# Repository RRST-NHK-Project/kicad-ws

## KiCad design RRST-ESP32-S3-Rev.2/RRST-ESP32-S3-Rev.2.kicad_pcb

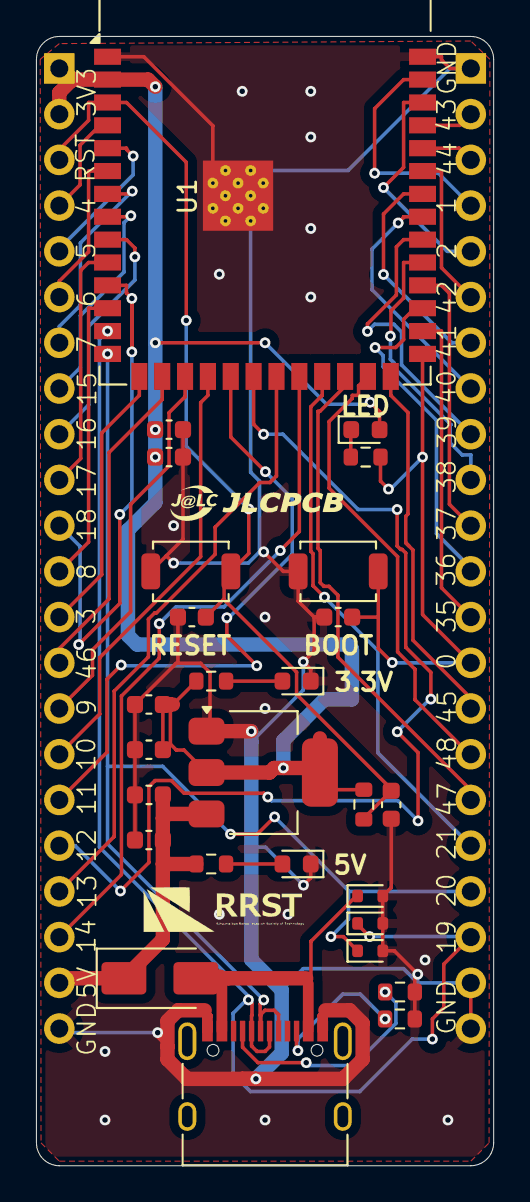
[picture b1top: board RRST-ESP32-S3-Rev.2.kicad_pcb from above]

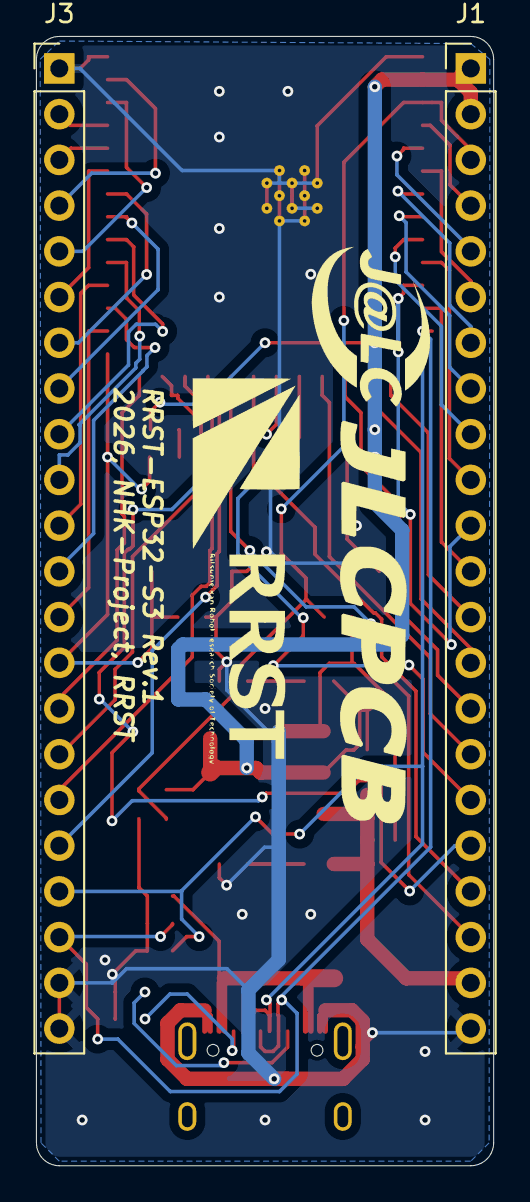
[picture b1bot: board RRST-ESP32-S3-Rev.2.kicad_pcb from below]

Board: 2 copper layers, 25.4 x 62.7 mm, 29 parts (2 on the bottom side), 46 nets.

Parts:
C1, C4, C5: 10uF; C_0603_1608Metric
C2, C3, C6, C7, C8: 100nF; C_0603_1608Metric
C9: 1uF; C_0603_1608Metric
D1, D3, D4: LED; LED_0603_1608Metric
D2: SS14; D_SMA
D5, D6, D8: LESD5D5.0CT1G; D_SOD-523
J1, J3: Conn_01x22_Pin; PinHeader_1x22_P2.54mm_Vertical
J2: USB_C_Receptacle_USB2.0_16P; USB_C_Receptacle_XKB_U262-16XN-4BVC11
R1, R2: 5.1k; R_0603_1608Metric
R3, R4: 5.1K; R_0603_1608Metric
R5: 10k; R_0603_1608Metric
R6: 330; R_0603_1608Metric
SW1, SW2: SW_Push; SW_SPST_TS-1088-xR020
U1: ESP32-S3-WROOM-1
U2: LD1117S33TR_SOT223; SOT-223-3_TabPin2

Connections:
3V3: C3.1, C4.1, C5.1, C6.1, D1.2 (A), J1.1, J1.2, R2.1, R5.1, U1.2 (3V3), U2.2 (VO)
+5V: C1.1, C2.1, D2.1 (K), J1.21, R1.1, U2.3 (VI)
DN: D6.1, J2.A7 (D-), J2.B7 (D-), J3.20, U1.13 (USB_D-)
DP: D8.1, J2.A6 (D+), J2.B6 (D+), J3.19, U1.14 (USB_D+)
EN: C7.1, C9.1, J1.3, R5.2, SW1.2, U1.3 (EN)
GND: C1.2, C2.2, C3.2, C4.2, C5.2, C6.2, C7.2, C8.2, C9.2, D3.1 (K), D4.1 (K), D5.2, D6.2, D8.2, J1.22, J2.A1 (GND), J2.A12 (GND), J2.B1 (GND), J2.B12 (GND), J3.1, J3.21, J3.22, R3.2, R4.2, SW1.1, SW2.1, U1.1 (GND), U1.40 (GND), U1.41 (GND), U2.1 (GND)
IO0: C8.1, J3.14, R6.2, SW2.2, U1.27 (IO0)
IO1: J3.4, U1.39 (IO1)
IO2: J3.5, U1.38 (IO2)
IO3: J1.13, U1.15 (IO3)
IO4: J1.4, U1.4 (IO4)
IO5: J1.5, U1.5 (IO5)
IO6: J1.6, U1.6 (IO6)
IO7: J1.7, U1.7 (IO7)
IO8: J1.12, U1.12 (IO8)
IO9: J1.15, U1.17 (IO9)
IO10: J1.16, U1.18 (IO10)
IO11: J1.17, U1.19 (IO11)
IO12: J1.18, U1.20 (IO12)
IO13: J1.19, U1.21 (IO13)
IO14: J1.20, U1.22 (IO14)
IO15: J1.8, U1.8 (IO15)
IO16: J1.9, U1.9 (IO16)
IO17: J1.10, U1.10 (IO17)
IO18: J1.11, U1.11 (IO18)
IO21: J3.18, U1.23 (IO21)
IO35: J3.13, U1.28 (IO35)
IO36: J3.12, U1.29 (IO36)
IO37: J3.11, U1.30 (IO37)
IO38: J3.10, U1.31 (IO38)
IO39: J3.9, U1.32 (IO39)
IO40: J3.8, U1.33 (IO40)
IO41: J3.7, U1.34 (IO41)
IO42: J3.6, U1.35 (IO42)
IO45: J3.15, U1.26 (IO45)
IO46: J1.14, U1.16 (IO46)
IO47: J3.17, U1.24 (IO47)
IO48: J3.16, U1.25 (IO48)
unnamed: D1.1 (K), R6.1
unnamed: D3.2 (A), R1.2
unnamed: D4.2 (A), R2.2
unnamed: J2.A5 (CC1), R4.1
unnamed: J2.B5 (CC2), R3.1
RXD0: J3.3, U1.36 (RXD0)
TXD0: J3.2, U1.37 (TXD0)
VBUS: D2.2 (A), D5.1, J2.A4 (VBUS), J2.A9 (VBUS), J2.B4 (VBUS), J2.B9 (VBUS)

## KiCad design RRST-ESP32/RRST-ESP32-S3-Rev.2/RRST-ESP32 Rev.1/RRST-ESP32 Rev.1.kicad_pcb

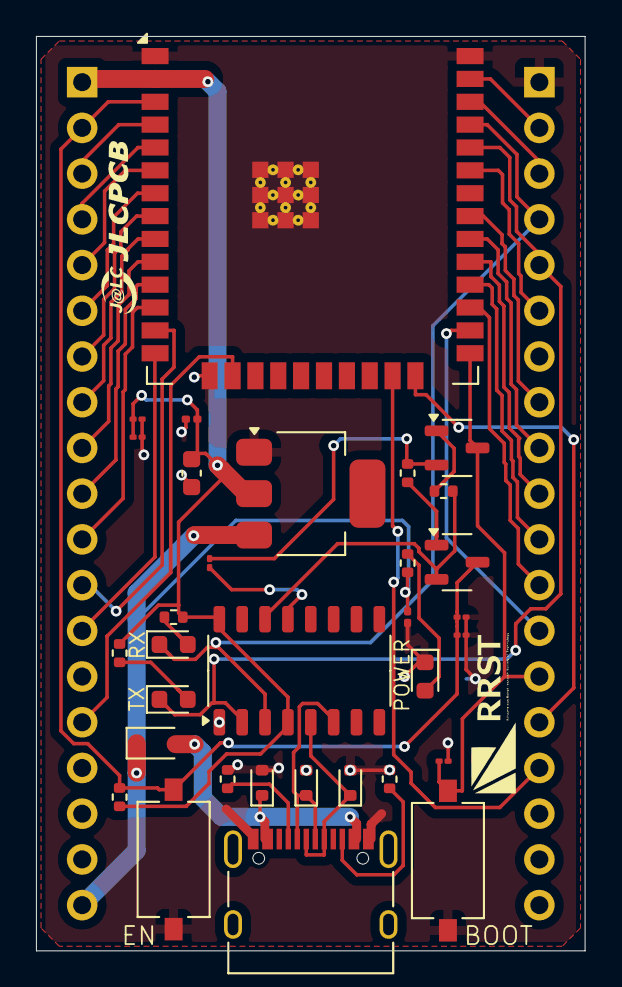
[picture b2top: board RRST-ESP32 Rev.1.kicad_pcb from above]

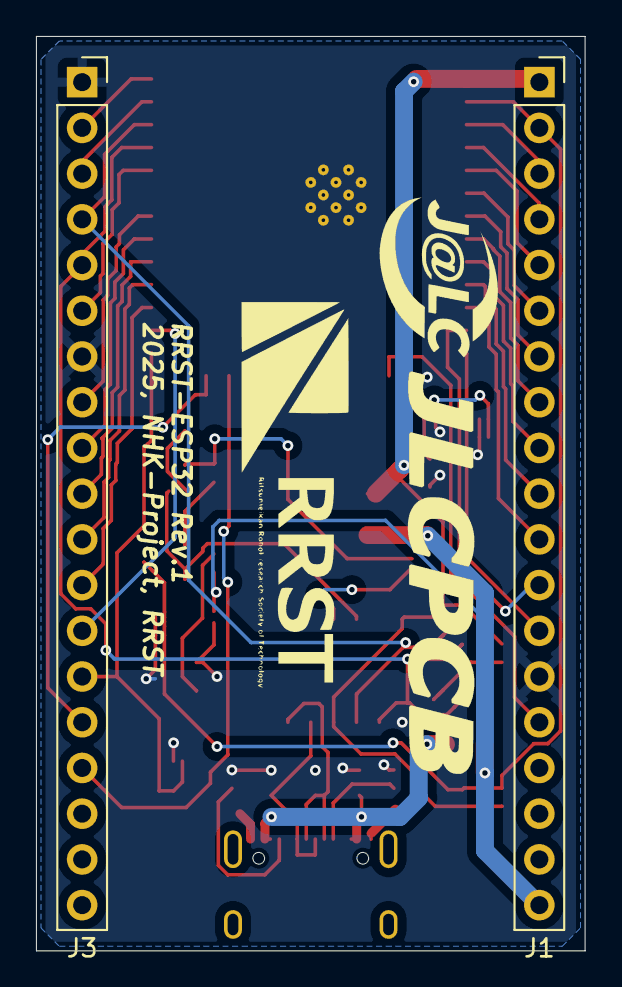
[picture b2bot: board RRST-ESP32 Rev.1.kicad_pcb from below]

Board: 2 copper layers, 30.5 x 50.8 mm, 34 parts (2 on the bottom side), 43 nets.

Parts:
C3: 22uF/10V(20%); C_0603_1608Metric
C4, C6, C7: 0.1uF/50V(10%); C_01005_0402Metric
C5: 0.1uF/50V(10%)(NC); C_01005_0402Metric
C8, C9: 22uF/10V(20%); C_0201_0603Metric
C10, C11: 100nF; C_01005_0402Metric
D1, D2, D4: LESD5D5.0CT1G; D_SOD-523
D3: BAT760-7; D_SOD-323
D5, D6, D7: LED; LED_0603_1608Metric
J1, J3: Conn_01x19_Pin; PinHeader_1x19_P2.54mm_Vertical
J2: USB_C_Receptacle_USB2.0_16P; USB_C_Receptacle_XKB_U262-16XN-4BVC11
Q1, Q2: SS8050-G; SOT-23-3
R1, R2: 1K; R_0402_1005Metric
R3, R4: 5.1K; R_0402_1005Metric
R5, R6, R17: 10K(5%); R_0402_1005Metric
R18: 2K(5%); R_0402_1005Metric
SW1, SW2: SW_Push; SW_Tactile_SPST_NO_Straight_CK_PTS636Sx25SMTRLFS
U1: CH340C; JEITA_SOIC-16_3.9x9.9mm_P1.27mm
U10: ESP32-WROOM-32E
U11: AMS1117-3.3; SOT-223

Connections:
DN: D2.1, J2.A7 (D-), J2.B7 (D-), U1.6 (UD-)
DP: D4.1, J2.A6 (D+), J2.B6 (D+), U1.5 (UD+)
DTR: C11.1, Q2.2, R5.2
EN: C4.1, C7.1, J1.2, Q1.3, R17.2, SW2.2, U10.3 (EN)
EXT_5V: C8.1, D3.C, J1.19, R18.1, U11.3 (VI)
GND: C3.2, C4.2, C5.2, C6.2, C7.2, C8.2, C9.2, C10.2, D1.2, D2.2, D4.2, D5.1 (K), J1.14, J2.A1 (GND), J2.A12 (GND), J2.B1 (GND), J2.B12 (GND), J3.1, J3.7, R3.2, R4.2, SW1.1, SW2.1, U1.1 (GND), U10.1 (GND), U10.15 (GND), U10.38 (GND), U10.39 (GND), U11.1 (GND)
IO0: C5.1, J3.14, Q2.3, SW1.2, U10.25 (IO0)
IO2: J3.15, U10.24 (IO2)
IO4: J3.13, U10.26 (IO4)
IO5: J3.10, U10.29 (IO5)
IO12: J1.13, U10.14 (IO12)
IO13: J1.15, U10.16 (IO13)
IO14: J1.12, U10.13 (IO14)
IO15: J3.16, U10.23 (IO15)
IO16: J3.12, U10.27 (IO16)
IO17: J3.11, U10.28 (IO17)
IO18: J3.9, U10.30 (IO18)
IO19: J3.8, U10.31 (IO19)
IO21: J3.6, U10.33 (IO21)
IO22: J3.3, U10.36 (IO22)
IO23: J3.2, U10.37 (IO23)
IO25: J1.9, U10.10 (IO25)
IO26: J1.10, U10.11 (IO26)
IO27: J1.11, U10.12 (IO27)
IO32: J1.7, U10.8 (IO32)
IO33: J1.8, U10.9 (IO33)
IO34: J1.5, U10.6 (IO34)
IO35: J1.6, U10.7 (IO35)
unnamed: D5.2 (A), R18.2
unnamed: D6.2 (A), R1.2
unnamed: D7.2 (A), R2.2
unnamed: J2.A5 (CC1), R4.1
unnamed: J2.B5 (CC2), R3.1
unnamed: Q1.1, R5.1
unnamed: Q2.1, R6.1
unnamed: C11.2, U1.13 (~DTR)
RTS: Q1.2, R6.2, U1.14 (~RTS)
RX: D6.1 (K), J3.4, U1.3 (RXD), U10.35 (TXD0/IO1)
RXD0/IO3: D7.1 (K), J3.5, U1.2 (TXD), U10.34 (RXD0/IO3)
SENSOR_VN: J1.4, U10.5 (SENSOR_VN)
SENSOR_VP: J1.3, U10.4 (SENSOR_VP)
VBUS: D1.1, D3.A, J2.A4 (VBUS), J2.A9 (VBUS), J2.B4 (VBUS), J2.B9 (VBUS)
VDD33: C3.1, C6.1, C9.1, C10.1, J1.1, R1.1, R2.1, R17.1, U1.4 (V3), U1.16 (VCC), U10.2 (VDD), U11.2 (VO)

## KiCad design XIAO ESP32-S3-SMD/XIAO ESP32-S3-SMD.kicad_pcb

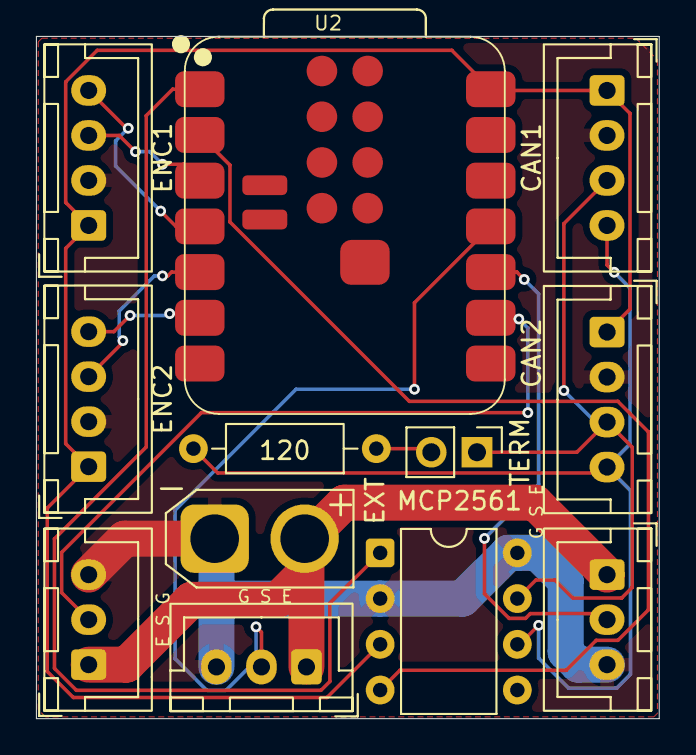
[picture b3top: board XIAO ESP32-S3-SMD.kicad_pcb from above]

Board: 2 copper layers, 34.6 x 37.9 mm, 13 parts (1 on the bottom side), 15 nets.

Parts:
120: 120; R_Axial_DIN0207_L6.3mm_D2.5mm_P10.16mm_Horizontal
CAN1, CAN2: Conn_01x04_Socket; JST_XH_B4B-XH-A_1x04_P2.50mm_Vertical
ENC1: ENC1; JST_XH_B4B-XH-A_1x04_P2.50mm_Vertical
ENC2: ENC2; JST_XH_B4B-XH-A_1x04_P2.50mm_Vertical
ESG1: Conn_01x03_Socket; JST_XH_B3B-XH-A_1x03_P2.50mm_Vertical
EXT: Conn_01x02_Pin; AMASS_XT30U-M_1x02_P5.0mm_Vertical
GSE2, GSE3: Conn_01x03_Socket; JST_XH_B3B-XH-A_1x03_P2.50mm_Vertical
MCP2561: DIP-8_W7.62mm
TERM: R120; PinHeader_1x02_P2.54mm_Vertical
U2: XIAO-ESP32-S3-SMD
soki: LOGO

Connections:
5V0: CAN1.1, CAN2.1, ENC1.1, ENC2.1, MCP2561.3 (Vdd), U2.14 (VBUS)
CANH: CAN1.3, CAN2.3, MCP2561.7 (CANH), TERM.1
CANL: 120.2, CAN1.4, CAN2.4, MCP2561.6 (CANL)
CAN_RX: MCP2561.4 (Rxd), U2.2 (GPIO2_A1_D1)
CAN_TX: MCP2561.1 (Txd), U2.1 (GPIO1_A0_D0)
ENC1_A: ENC1.3, U2.3 (GPIO3_A2_D2)
ENC1_B: ENC1.4, U2.4 (GPIO4_A3_D3)
ENC2_A: ENC2.3, U2.5 (GPIO5_A4_D4_SDA)
ENC2_B: ENC2.4, U2.6 (GPIO6_A5_D5_SCL)
EXT_POWER: ESG1.1, EXT.2, GSE2.1, GSE3.1
GND: CAN1.2, CAN2.2, ENC1.2, ENC2.2, ESG1.3, EXT.1, GSE2.3, GSE3.3, MCP2561.2 (Vss), MCP2561.8 (STBY), U2.13 (GND)
GPIO7: ESG1.2, U2.9 (GPIO7_A8_D8_SCK)
GPIO8: GSE2.2, U2.10 (GPIO8_A9_D9_MISO)
GPIO9: GSE3.2, U2.11 (GPIO9_A10_D10_MOSI)
unnamed: 120.1, TERM.2

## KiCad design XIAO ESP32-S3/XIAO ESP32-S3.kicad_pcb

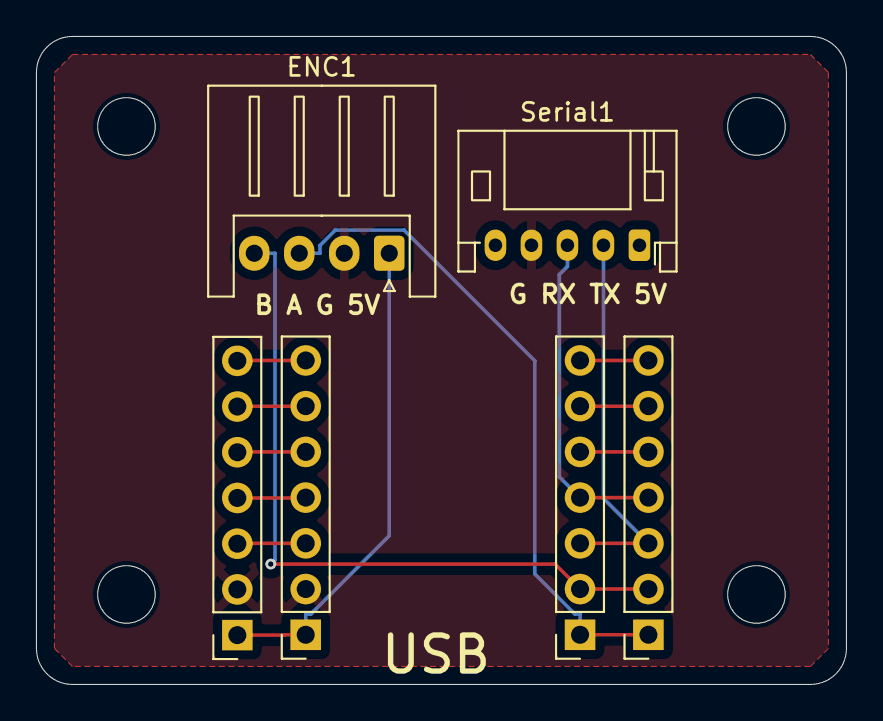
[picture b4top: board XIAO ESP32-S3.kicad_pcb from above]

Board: 2 copper layers, 45.0 x 36.0 mm, 10 parts (0 on the bottom side), 14 nets.

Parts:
ENC1: ENC1; JST_XH_S4B-XH-A_1x04_P2.50mm_Horizontal
J1, J2, J3, J4: Conn_01x07_Socket; PinSocket_1x07_P2.54mm_Vertical
REF1**, REF2**, REF3**, REF4**: MountingHole_3.2mm_M3
Serial1: Serial1; JST_PH_S5B-PH-K_1x05_P2.00mm_Horizontal

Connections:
3V3: J2.3, J4.3
5V: ENC1.1, J2.1, J4.1
ENC1_A: ENC1.3, J1.1, J3.1
ENC1_B: ENC1.4, J1.2, J3.2
GND: ENC1.2, J2.2, J4.2, Serial1.4
GPIO3: J1.3, J3.3, Serial1.2
GPIO4: J1.4, J3.4, Serial1.3
GPIO7: J2.6, J4.6
GPIO8: J2.5, J4.5
NC1: J1.5, J3.5
NC2: J1.6, J3.6
NC3: J1.7, J3.7
NC4: J2.4, J4.4
NC5: J2.7, J4.7

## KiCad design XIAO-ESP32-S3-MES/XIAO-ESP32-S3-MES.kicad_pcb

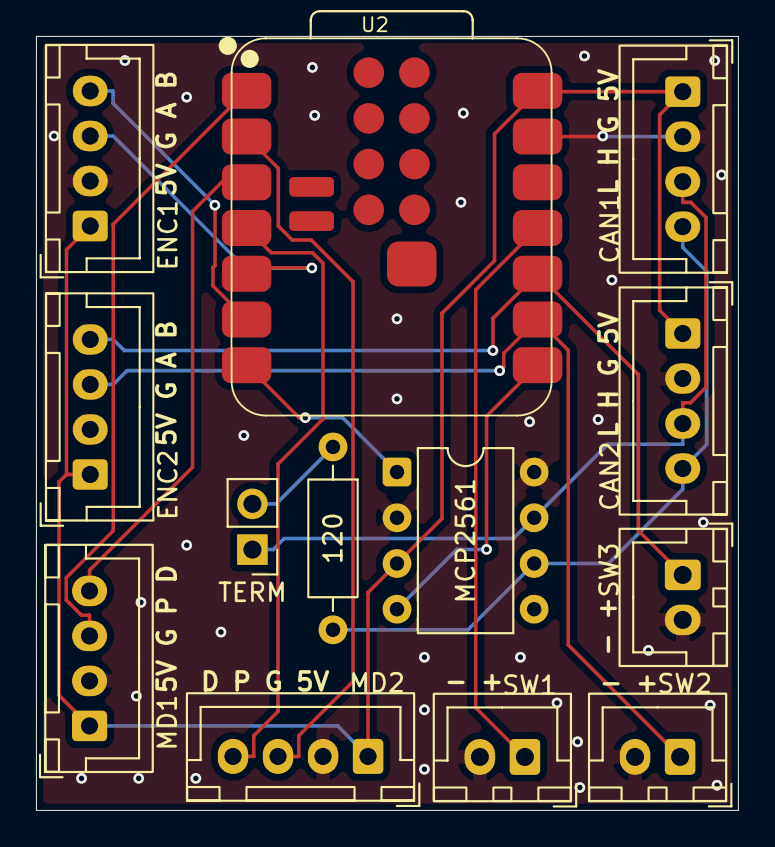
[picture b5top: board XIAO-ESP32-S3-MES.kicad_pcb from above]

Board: 2 copper layers, 39.0 x 43.0 mm, 13 parts (0 on the bottom side), 16 nets.

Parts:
CAN1, CAN2: Conn_01x04_Socket; JST_XH_B4B-XH-A_1x04_P2.50mm_Vertical
ENC1: ENC1; JST_XH_B4B-XH-A_1x04_P2.50mm_Vertical
ENC2: ENC2; JST_XH_B4B-XH-A_1x04_P2.50mm_Vertical
MD1: MD1; JST_XH_B4B-XH-A_1x04_P2.50mm_Vertical
MD2: MD2; JST_XH_B4B-XH-A_1x04_P2.50mm_Vertical
R1: 120; R_Axial_DIN0207_L6.3mm_D2.5mm_P10.16mm_Horizontal
SW1: SW1; JST_XH_B2B-XH-A_1x02_P2.50mm_Vertical
SW2: SW2; JST_XH_B2B-XH-A_1x02_P2.50mm_Vertical
SW3: SW3; JST_XH_B2B-XH-A_1x02_P2.50mm_Vertical
TERM: R120; PinHeader_1x02_P2.54mm_Vertical
U1: DIP-8_W7.62mm
U2: XIAO-ESP32-S3-SMD

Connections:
5V0: CAN1.1, CAN2.1, ENC1.1, ENC2.1, MD1.1, MD2.1, U1.3 (Vdd), U2.14 (VBUS)
CANH: CAN1.3, CAN2.3, TERM.1, U1.7 (CANH)
CANL: CAN1.4, CAN2.4, R1.2, U1.6 (CANL)
CAN_RX: U1.4 (Rxd), U2.8 (GPIO44_D7_RX)
CAN_TX: U1.1 (Txd), U2.7 (GPIO43_D6_TX)
ENC1_A: ENC1.3, U2.5 (GPIO5_A4_D4_SDA)
ENC1_B: ENC1.4, U2.6 (GPIO6_A5_D5_SCL)
ENC2_A/SW2: ENC2.3, SW2.1, U2.9 (GPIO7_A8_D8_SCK)
ENC2_B/SW3: ENC2.4, SW3.1, U2.10 (GPIO8_A9_D9_MISO)
GND: CAN1.2, CAN2.2, ENC1.2, ENC2.2, MD1.2, MD2.2, SW1.2, SW2.2, SW3.2, U1.2 (Vss), U1.8 (STBY), U2.13 (GND)
GPIO1: MD1.3, U2.1 (GPIO1_A0_D0)
GPIO2: MD2.3, U2.2 (GPIO2_A1_D1)
GPIO3: MD1.4, U2.3 (GPIO3_A2_D2)
GPIO4: MD2.4, U2.4 (GPIO4_A3_D3)
GPIO9: SW1.1, U2.11 (GPIO9_A10_D10_MOSI)
unnamed: R1.1, TERM.2

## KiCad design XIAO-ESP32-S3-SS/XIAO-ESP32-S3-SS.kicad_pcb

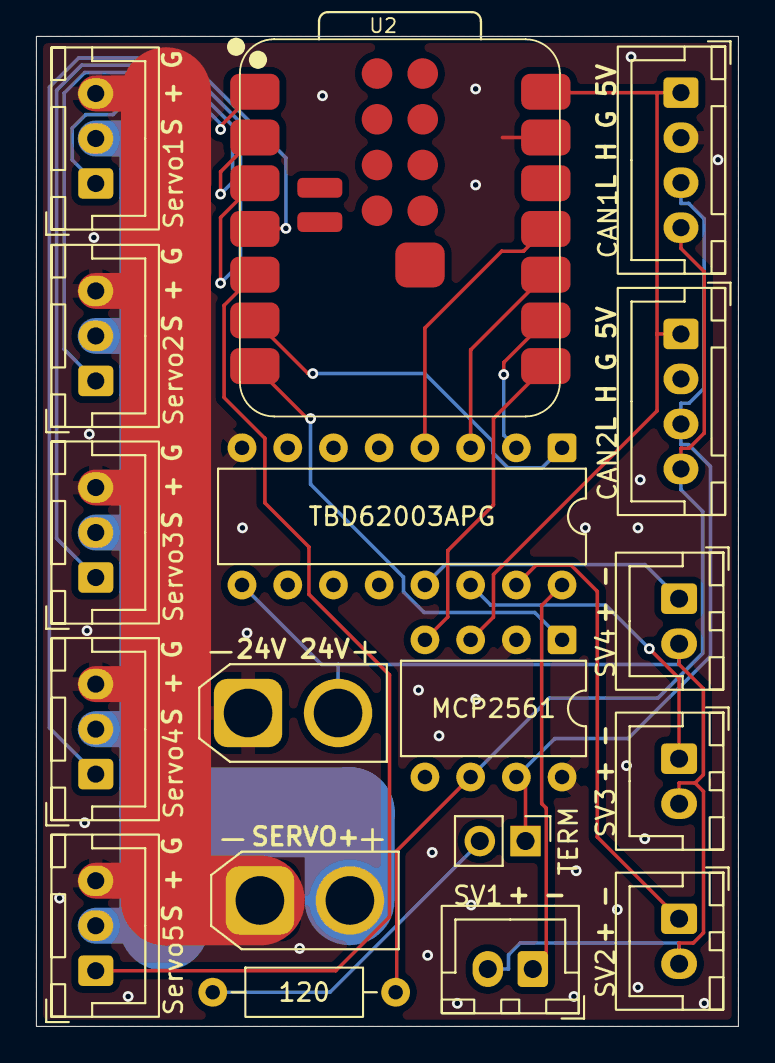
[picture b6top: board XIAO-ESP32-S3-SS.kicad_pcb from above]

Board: 2 copper layers, 39.0 x 55.0 mm, 18 parts (0 on the bottom side), 22 nets.

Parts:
24V 24V: Conn_01x02_Pin; AMASS_XT30U-M_1x02_P5.0mm_Vertical
CAN1, CAN2: Conn_01x04_Socket; JST_XH_B4B-XH-A_1x04_P2.50mm_Vertical
R1: 120; R_Axial_DIN0207_L6.3mm_D2.5mm_P10.16mm_Horizontal
SERVO+: Conn_01x02_Pin; AMASS_XT30U-M_1x02_P5.0mm_Vertical
SV1: SV1; JST_XH_B2B-XH-A_1x02_P2.50mm_Vertical
SV2: SV2; JST_XH_B2B-XH-A_1x02_P2.50mm_Vertical
SV3: SV3; JST_XH_B2B-XH-A_1x02_P2.50mm_Vertical
SV4: SV4; JST_XH_B2B-XH-A_1x02_P2.50mm_Vertical
Servo1: Servo1; JST_XH_B3B-XH-A_1x03_P2.50mm_Vertical
Servo2: Servo2; JST_XH_B3B-XH-A_1x03_P2.50mm_Vertical
Servo3: Servo3; JST_XH_B3B-XH-A_1x03_P2.50mm_Vertical
Servo4: Servo4; JST_XH_B3B-XH-A_1x03_P2.50mm_Vertical
Servo5: Servo5; JST_XH_B3B-XH-A_1x03_P2.50mm_Vertical
TERM: R120; PinHeader_1x02_P2.54mm_Vertical
U1: DIP-8_W7.62mm
U2: XIAO-ESP32-S3-SMD
U3: DIP-16_W7.62mm

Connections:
5V0: CAN1.1, CAN2.1, U1.3 (Vdd), U2.14 (VBUS)
+24V: 24V 24V.2, SV1.2, SV2.2, SV3.2, SV4.2, U3.9 (COMMON)
CANH: CAN1.3, CAN2.3, TERM.1, U1.7 (CANH)
CANL: CAN1.4, CAN2.4, R1.2, U1.6 (CANL)
CAN_RX: U1.4 (Rxd), U2.8 (GPIO44_D7_RX)
CAN_TX: U1.1 (Txd), U2.7 (GPIO43_D6_TX)
GND: 24V 24V.1, CAN1.2, CAN2.2, SERVO+.1, Servo1.3, Servo2.3, Servo3.3, Servo4.3, Servo5.3, U1.2 (Vss), U1.8 (STBY), U2.13 (GND), U3.8 (GND)
GPIO1: Servo1.1, U2.1 (GPIO1_A0_D0)
GPIO2: Servo2.1, U2.2 (GPIO2_A1_D1)
GPIO3: Servo3.1, U2.3 (GPIO3_A2_D2)
GPIO4: Servo4.1, U2.4 (GPIO4_A3_D3)
GPIO5: Servo5.1, U2.5 (GPIO5_A4_D4_SDA)
GPIO6: U2.6 (GPIO6_A5_D5_SCL), U3.1 (I1)
GPIO7: U2.9 (GPIO7_A8_D8_SCK), U3.2 (I2)
GPIO8: U2.10 (GPIO8_A9_D9_MISO), U3.3 (I3)
GPIO9: U2.11 (GPIO9_A10_D10_MOSI), U3.4 (I4)
unnamed: R1.1, TERM.2
O1: SV1.1, U3.16 (O1)
O2: SV2.1, U3.15 (O2)
O3: SV3.1, U3.14 (O3)
O4: SV4.1, U3.13 (O4)
SERVO+: SERVO+.2, Servo1.2, Servo2.2, Servo3.2, Servo4.2, Servo5.2
